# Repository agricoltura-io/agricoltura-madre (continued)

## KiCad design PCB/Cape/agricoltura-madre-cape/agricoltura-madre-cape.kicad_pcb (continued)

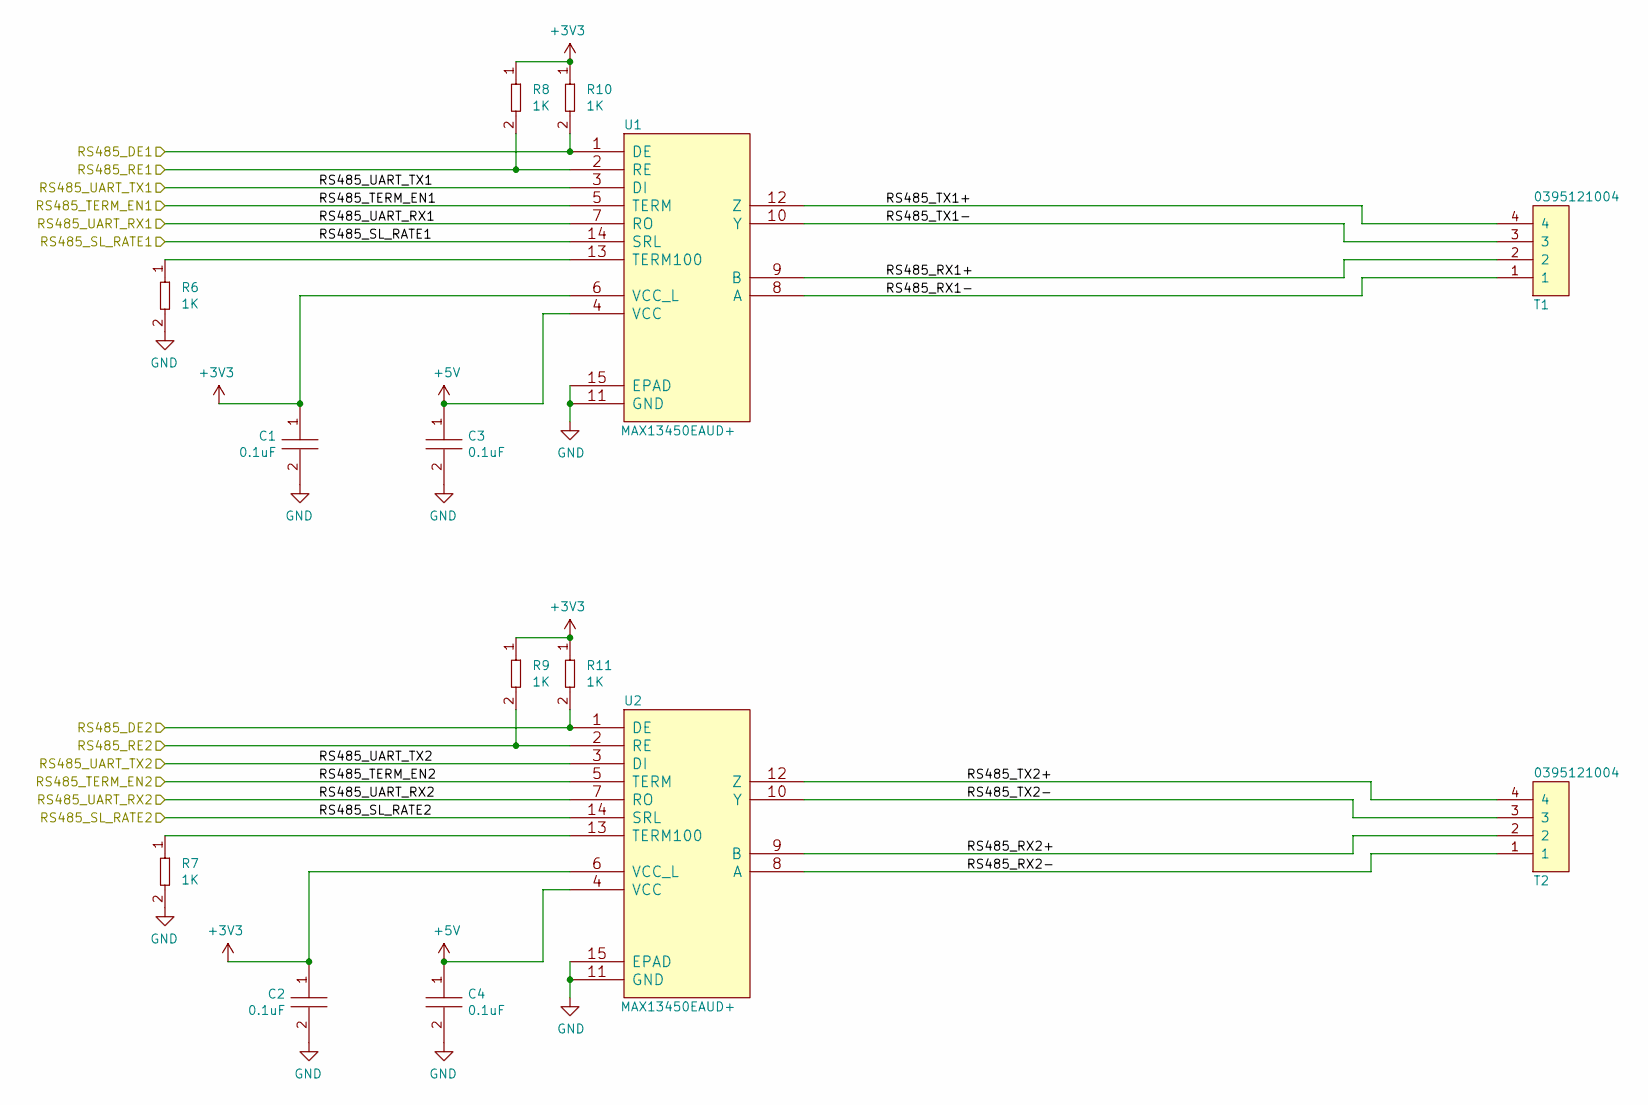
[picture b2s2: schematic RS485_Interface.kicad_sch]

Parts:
C1, C2: C0402C104K9PACTU; R0402; Tolerance 10%; Voltage 6.3V; MFR# C0402C104K9PACTU
C3, C4: CGA3E2X7R1H104K080AA; C0603; Tolerance 10%; Voltage 50V; MFR# CGA3E2X7R1H104K080AA
R6, R7, R8, R9, R10, R11: RC0402FR-071KL; R0402; Tolerance 1%; Voltage *; MFR# RC0402FR-071KL
T1, T2: 0395121004; Tolerance *; Voltage 300V; MFR# 0395121004
U1, U2: MAX13450EAUD+; MAX13450EAUD&plus_; Tolerance *; Voltage 4.75V ~ 5.25V; MFR# MAX13450EAUD+

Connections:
+3V3: C1.1, C2.1, R8.1, R9.1, R10.1, R11.1, U1.6 (VCC_L), U2.6 (VCC_L); also elsewhere on the board
+5V: C3.1, C4.1, U1.4 (VCC), U2.4 (VCC); also elsewhere on the board
/Beaglebone Interface/RS485_DE1: R10.2, U1.1 (DE); also elsewhere on the board
/Beaglebone Interface/RS485_DE2: R11.2, U2.1 (DE); also elsewhere on the board
/Beaglebone Interface/RS485_RE1: R8.2, U1.2 (RE); also elsewhere on the board
/Beaglebone Interface/RS485_RE2: R9.2, U2.2 (RE); also elsewhere on the board
/Beaglebone Interface/RS485_SL_RATE1: U1.14 (SRL); also elsewhere on the board
/Beaglebone Interface/RS485_SL_RATE2: U2.14 (SRL); also elsewhere on the board
/Beaglebone Interface/RS485_TERM_EN1: U1.5 (TERM); also elsewhere on the board
/Beaglebone Interface/RS485_TERM_EN2: U2.5 (TERM); also elsewhere on the board
/Beaglebone Interface/RS485_UART_RX1: U1.7 (RO); also elsewhere on the board
/Beaglebone Interface/RS485_UART_RX2: U2.7 (RO); also elsewhere on the board
/Beaglebone Interface/RS485_UART_TX1: U1.3 (DI); also elsewhere on the board
/Beaglebone Interface/RS485_UART_TX2: U2.3 (DI); also elsewhere on the board
/RS485 Interface/RS485_RX1+: T1.2, U1.9 (B)
/RS485 Interface/RS485_RX1-: T1.1, U1.8 (A)
/RS485 Interface/RS485_RX2+: T2.2, U2.9 (B)
/RS485 Interface/RS485_RX2-: T2.1, U2.8 (A)
/RS485 Interface/RS485_TX1+: T1.4, U1.12 (Z)
/RS485 Interface/RS485_TX1-: T1.3, U1.10 (Y)
/RS485 Interface/RS485_TX2+: T2.4, U2.12 (Z)
/RS485 Interface/RS485_TX2-: T2.3, U2.10 (Y)
GND: C1.2, C2.2, C3.2, C4.2, R6.2, R7.2, U1.11 (GND), U1.15 (EPAD), U2.11 (GND), U2.15 (EPAD); also elsewhere on the board
unnamed: R6.1, U1.13 (TERM100)
unnamed: R7.1, U2.13 (TERM100)

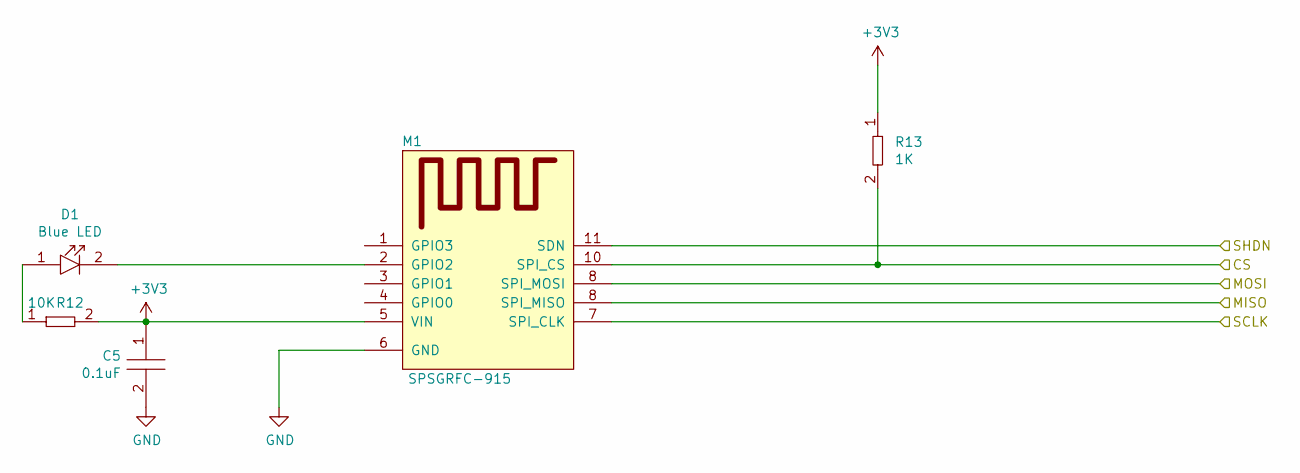
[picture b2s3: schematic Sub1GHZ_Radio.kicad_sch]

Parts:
C5: C0402C104K9PACTU; R0402; Tolerance 10%; Voltage 6.3V; MFR# C0402C104K9PACTU
D1: LTST-C194TBKT; LED0603; Tolerance *; Voltage 3.3V; MFR# LTST-C194TBKT
M1: SPSGRFC-915; XCVR_SPSGRF-915; Tolerance *; Voltage 1.8V ~ 3.6V; MFR# SPSGRFC-915
R12: RC0402FR-0710KL; R0402; Tolerance 1%; Voltage *; MFR# RC0402FR-0710KL
R13: RC0402FR-071KL; R0402; Tolerance 1%; Voltage *; MFR# RC0402FR-071KL

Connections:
+3V3: C5.1, M1.5 (VIN), R12.2, R13.1; also elsewhere on the board
/915MHZ Radio/Modem/CS: M1.10 (SPI_CS), R13.2; also elsewhere on the board
/915MHZ Radio/Modem/MISO: M1.8 (SPI_MISO); also elsewhere on the board
/915MHZ Radio/Modem/SCLK: M1.7 (SPI_CLK); also elsewhere on the board
/915MHZ Radio/Modem/SHDN: M1.11 (SDN); also elsewhere on the board
GND: C5.2, M1.6 (GND); also elsewhere on the board
unnamed: D1.1, R12.1
unnamed: D1.2, M1.2 (GPIO2)

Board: 2 copper layers, 30 parts (0 on the bottom side), 38 nets, no tracks yet.

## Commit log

2020-06-30 BBG Cape
    Started KiCAD project for BBG cape version. Two RS485 ports using same transceiver as Vine directly wired to BBG serial ports. SPI to UART bridge for radios to follow.
2020-07-02 Added UAR Bridge
    Started SPI to UART bridge schematic, still researching part
2020-07-07 SPI UART Bridge
    Fleshed out schematic for SPI UART bridge chip, realized we may not need it, now going to fork project and develop two versions in this same repository.
2020-07-07 RPi4 Version and Cape Fork
    Forked the Beaglebone Green Cape version of madre, there are now two variants, one with the SPI to 4 UART bridge and one without that will talk to all Radios/Modems via SPI directly using spare IO pi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
    RPi4 hat version created from a past project, performed all the basic modifications to the schematic to creat the pi version of madre, this one is the most developed version at the moment.
2020-07-07 SBC Documentation
    Added all documentaion for RPi4, BBG, and BBG-Gateway.
2020-07-08 Datasheets and BBG version
    Finished initial schematic for BBG Gateway version and added datasheets for ST sub 1GHZ RF hardware.
2020-07-08 RPi version PSU
    updated POE circuit with fixed footprint for rectifier diodes.
2020-08-18 Board Work
    Board shape added working on cut outs
2024-03-26 Create license.md
    Added license
2024-03-26 KiCAD 8
    Projected updated to KiCAD 8
